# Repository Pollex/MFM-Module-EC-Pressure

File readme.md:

## TODOs

### Open Q's
- [ ] Calibration must happens when probe is switched. When and how to do this?
- [ ] Is it worth disabling the EZO circuit LED?
  - Perhaps sending the command takes more power than the LED being on

### Atlas Scientific EZO Circuit
- [ ] Send probe K value from EEPROM in perform_measurement
- [ ] Send calibration string from EEPROM in perform_measurement
- [ ] Send water temperature from EEPROM in perform_measurement

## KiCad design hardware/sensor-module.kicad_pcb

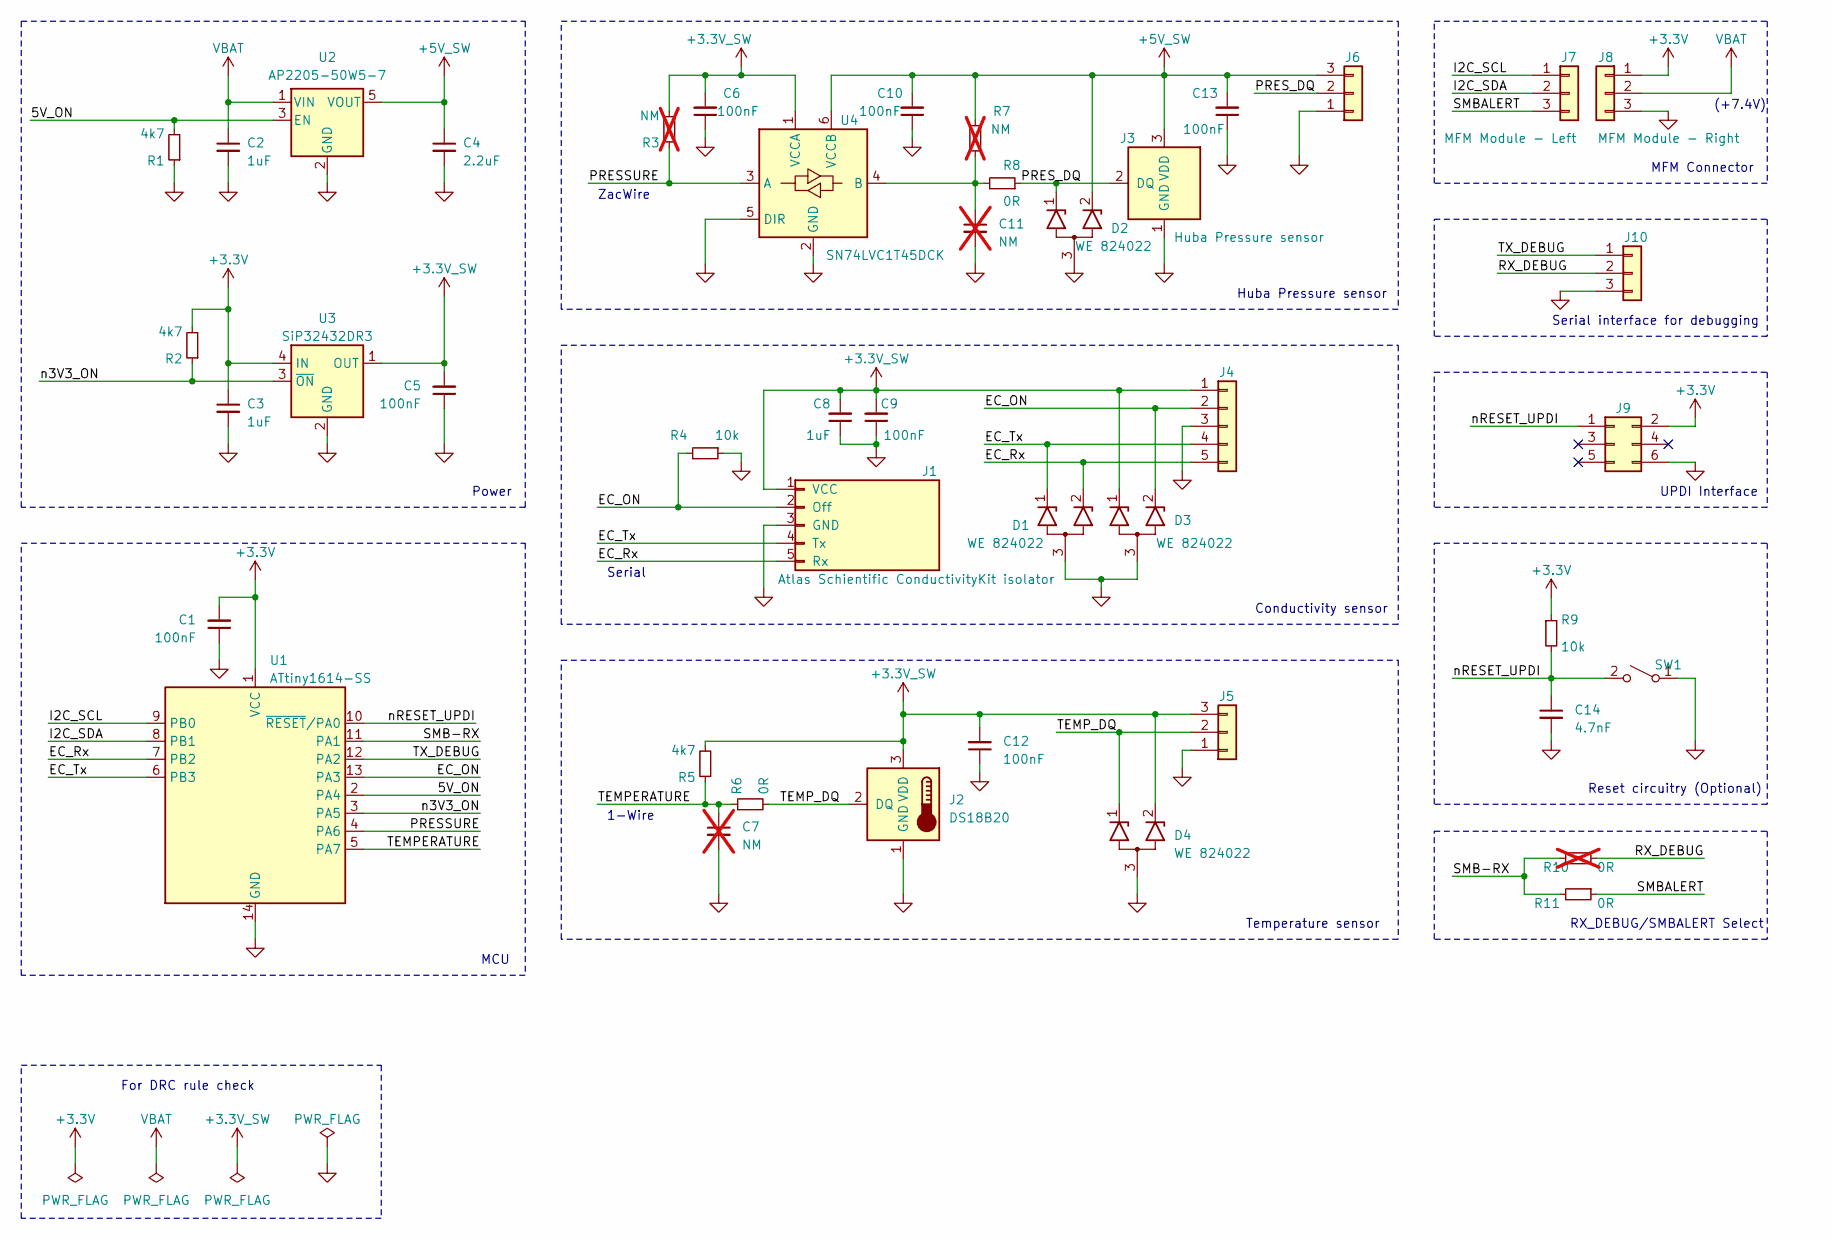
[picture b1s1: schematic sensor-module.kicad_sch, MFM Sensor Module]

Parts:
C1, C5, C6, C9, C10, C12, C13: 100nF; C_0603_1608Metric
C2, C3, C8: 1uF; C_0805_2012Metric
C4: 2.2uF; C_0805_2012Metric
C7, C11: NM; C_0603_1608Metric; not fitted
C14: 4.7nF; C_0603_1608Metric
D1, D2, D3, D4: WE 824022; SOT-23-3L
J1: Atlas Schientific ConductivityKit isolator; TerminalBlock_Phoenix_MPT-0,5-5-2.54_1x05_P2.54mm_Horizontal
J2: DS18B20; TerminalBlock_Phoenix_MPT-0,5-3-2.54_1x03_P2.54mm_Horizontal
J3: Huba Pressure sensor; TerminalBlock_Phoenix_MPT-0,5-3-2.54_1x03_P2.54mm_Horizontal
J4: Conductivity; PinHeader_1x05_P2.54mm_Vertical
J5: Temperature; PinHeader_1x03_P2.54mm_Vertical
J6: Huba Pressure; PinHeader_1x03_P2.54mm_Vertical
J7: MFM Module - Left; PinHeader_1x03_P2.54mm_Vertical
J8: MFM Module - Right; PinHeader_1x03_P2.54mm_Vertical
J9: UPDI Interface; PinHeader_2x03_P2.54mm_Vertical
J10: Debug UART; PinHeader_1x03_P2.54mm_Vertical
R1, R2, R5: 4k7; C_0603_1608Metric
R3, R7: NM; C_0603_1608Metric; not fitted
R4, R9: 10k; C_0603_1608Metric
R6, R8, R11: 0R; C_0603_1608Metric
R10: 0R; C_0603_1608Metric; not fitted
SW1: PTS636 SM43 SMTR LFS; SW_Tactile_SPST_NO_Straight_CK_PTS636Sx25SMTRLFS
U1: ATtiny1614-SS; SOIC-14_3.9x8.7mm_P1.27mm
U2: AP2205-50W5-7; SOT-23-5
U3: SiP32432DR3; SOT-363_SC-70-6
U4: SN74LVC1T45DCK; SOT-363_SC-70-6

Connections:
+3.3V: C1.2, C3.1, J8.1, J9.2, R2.2, R9.1, U1.1 (VCC), U3.4 (IN)
+3.3V_SW: C5.2, C6.2, C8.2, C9.2, C12.2, D3.1 (K1), D4.2 (K2), J1.1 (VCC), J2.3 (VDD), J4.1, J5.3, R3.2, R5.2, U3.1 (OUT), U4.1 (VCCA)
+5V_SW: C4.1, C10.2, C13.2, D2.2 (K2), J3.3 (VDD), J6.3, R7.2, U2.5 (VOUT), U4.6 (VCCB)
/5V_ON: R1.2, U1.2 (PA4), U2.3 (EN)
/EC_ON: D3.2 (K2), J1.2 (Off), J4.2, R4.2, U1.13 (PA3)
/EC_Rx: D1.2 (K2), J1.5 (Rx), J4.5, U1.7 (PB2)
/EC_Tx: D1.1 (K1), J1.4 (Tx), J4.4, U1.6 (PB3)
/I2C_SCL: J7.1, U1.9 (PB0)
/I2C_SDA: J7.2, U1.8 (PB1)
/PRESSURE: R3.1, U1.4 (PA6), U4.3 (A)
/PRES_DQ: D2.1 (K1), J3.2 (DQ), J6.2, R8.1
/RX_DEBUG: J10.2, R10.1
/SMB-RX: R10.2, R11.2, U1.11 (PA1)
/SMBALERT: J7.3, R11.1
/TEMPERATURE: C7.1, R5.1, R6.1, U1.5 (PA7)
/TEMP_DQ: D4.1 (K1), J2.2 (DQ), J5.2, R6.2
/TX_DEBUG: J10.1, U1.12 (PA2)
/n3V3_ON: R2.1, U1.3 (PA5), U3.3 (~ON)
/nRESET_UPDI: C14.1, J9.1, R9.2, SW1.2 (B), U1.10 (~RESET/PA0)
GND: C1.1, C2.2, C3.2, C4.2, C5.1, C6.1, C7.2, C8.1, C9.1, C10.1, C11.2, C12.1, C13.1, C14.2, D1.3 (A), D2.3 (A), D3.3 (A), D4.3 (A), J1.3 (GND), J2.1 (GND), J3.1 (GND), J4.3, J5.1, J6.1, J8.3, J9.6, J10.3, R1.1, R4.1, SW1.1 (A), U1.14 (GND), U2.2 (GND), U3.2 (GND), U3.5 (GND), U4.2 (GND), U4.5 (DIR)
unnamed: C11.1, R7.1, R8.2, U4.4 (B)
VBAT: C2.1, J8.2, U2.1 (VIN)

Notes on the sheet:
Serial
Conductivity sensor
1-Wire
Huba Pressure sensor
Serial interface for debugging
Temperature sensor
ZacWire
RX_DEBUG/SMBALERT Select
(+7.4V)
For DRC rule check
MCU
MFM Connector
Power
UPDI Interface
Reset circuitry (Optional)

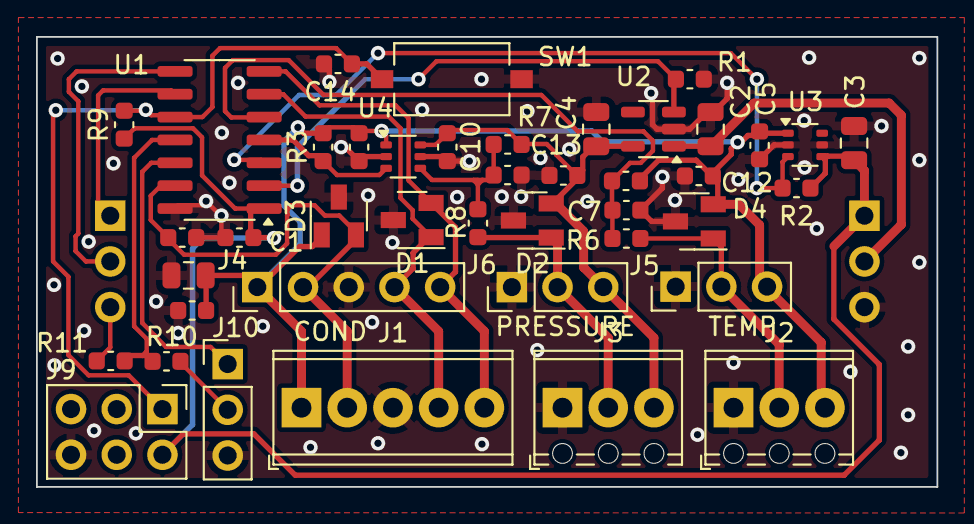
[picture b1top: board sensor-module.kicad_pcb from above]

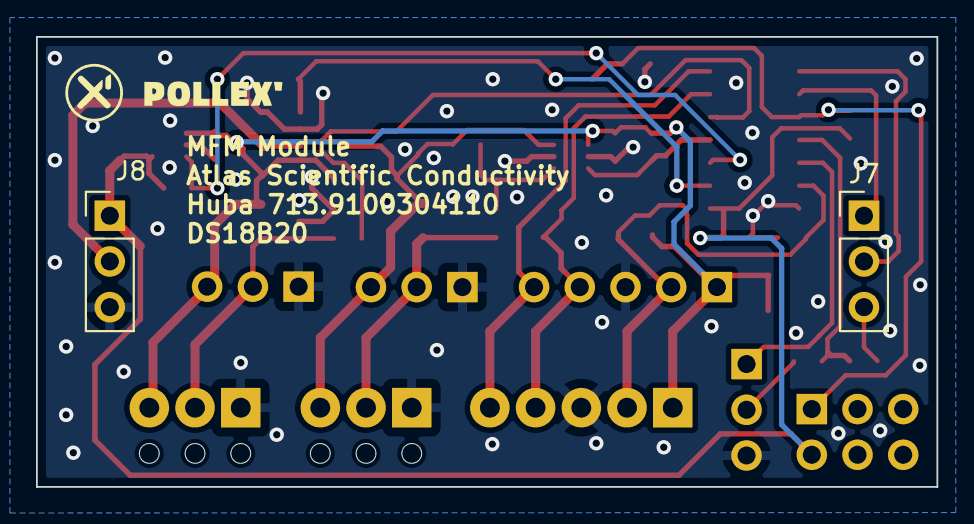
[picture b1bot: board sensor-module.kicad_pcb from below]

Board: 2 copper layers, 50.0 x 25.0 mm, 44 parts (2 on the bottom side), 22 nets.

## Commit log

2024-02-19 Update readme with todos
2024-02-21 update todo's
2024-02-21 Increase value string for ec sensor
2024-02-22 Test INT/TMR driven Zacwire (fail)
2024-02-23 Implement ZACWire with duty cycle calibration
2024-02-23 Change value copy logic
2024-03-05 Implement calibration and temp compensation
2024-03-05 fix(twi): avoid double handler execution
2024-03-05 fix(ec): calibrate during measurement, fix invalid buf
2024-03-07 feat(huba): add median filter
2024-03-29 Fix: Zacwire parity, Huba median calculation
2024-03-29 Chore: Update Kicad file version
2024-04-10 Hardware: add screw terminals
2025-09-11 kicad version upgrade, add ignores, add missing import
2025-09-11 disable EC features
